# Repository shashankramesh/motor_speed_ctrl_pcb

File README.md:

# motor_speed_ctrl_pcb

The repository contains the schematic, PCB layout, arduino code and simulation of the motor speed controller.

The speed controller uses ATmega328P-PU SMD microcontroller and includes I2C/SPI/USART communication.
The PCB is also designed to be interfaced with incremental, absolute or potentiometer speed sensors. 
Two or more speed controllers can be daisy chained with I2C communication.

The arduino code uses the PID algorithm for controlling the speed of the motors.

The simulation uses continous and discrete models of the motor whose speed had to be controlled, for tuning the parameters of PID. 
This motor model can be replaced with the model of the motor that has to be controlled.

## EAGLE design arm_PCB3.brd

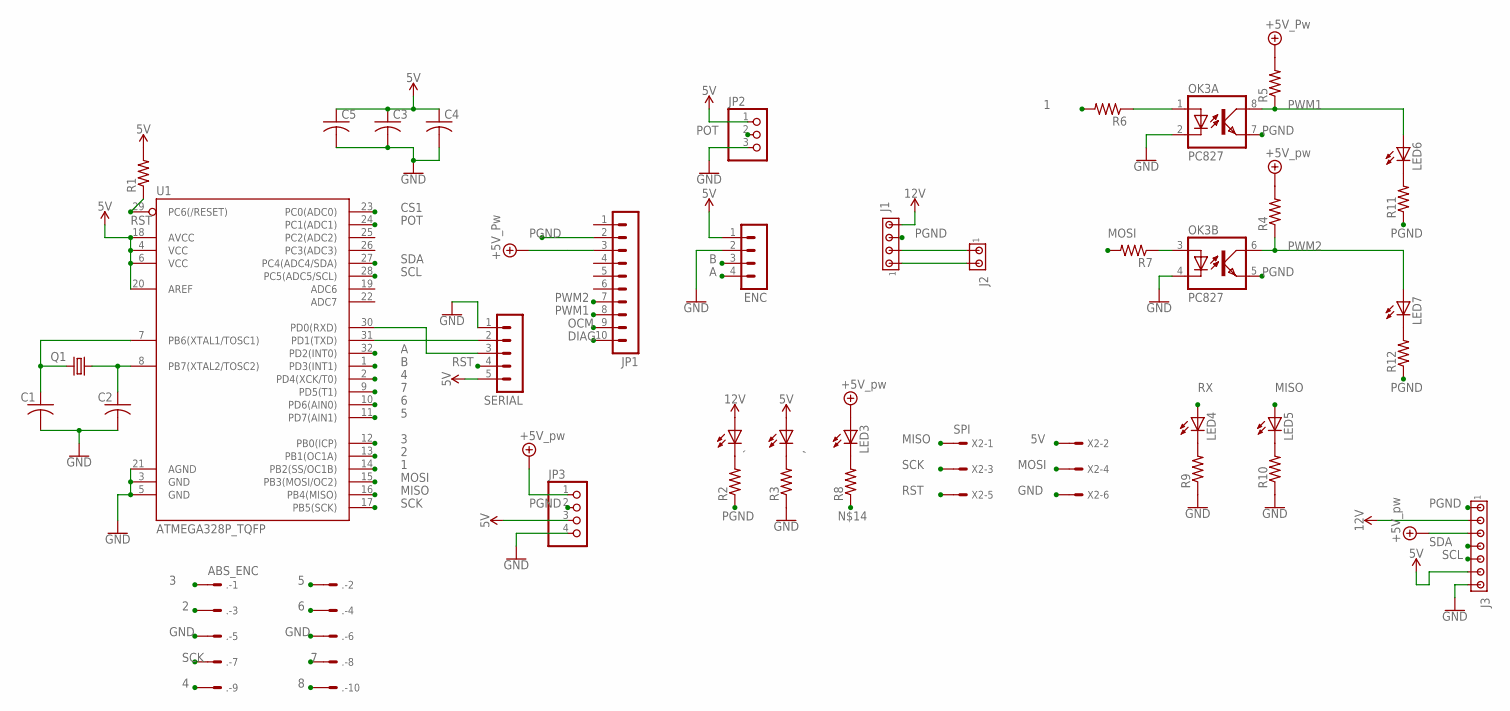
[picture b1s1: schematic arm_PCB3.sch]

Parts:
,: LEDSMT1206; 1206
.: ABS_ENC; 057-010-1
C1, C2: C-US025-024X044; C025-024X044
C3, C4, C5: C-USC1206; C1206
ENC: MA04-1
J1: MTA04-100; 10X04MTA
J2: MTA02-156; 1X2MTA
J3: MTA07-156; 1X7MTA
JP1: MA10-1
JP2: PINHD-1X3; 1X03
JP3: PINHD-1X4; 1X04
LED3, LED4, LED5, LED6, LED7: LEDSMT1206; 1206
OK3: PC827; DIL08
Q1: CRYSTALHC49U-V; HC49U-V
R1, R2, R3, R4, R5, R6, R7, R8, R9, R10, R11, R12: R-US_R0805; R0805
SERIAL: MA05-1
U1: ATMEGA328P_TQFP; TQFP32-08
X2: SPI; 057-006-1
`: LEDSMT1206; 1206

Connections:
1: R6.2, U1.14 (PB2(SS/OC1B))
2: ..3, U1.13 (PB1(OC1A))
3: ..1, U1.12 (PB0(ICP))
4: ..9, U1.2 (PD4(XCK/T0))
5: ..2, U1.11 (PD7(AIN1))
5V: ,.A, C3.1, C4.1, C5.1, ENC.1, J3.6, JP2.1, JP3.3, R1.2, SERIAL.5, U1.4 (VCC), U1.6 (VCC), U1.18 (AVCC), U1.20 (AREF), X2.2
6: ..4, U1.10 (PD6(AIN0))
7: ..8, U1.9 (PD5(T1))
8: ..10
12V: J1.4, J3.2, `.A
+5V: J3.3, JP1.3, JP3.1, LED3.A, R4.2, R5.2
A: ENC.4, U1.32 (PD2(INT0))
B: ENC.3, U1.1 (PD3(INT1))
CS1: U1.23 (PC0(ADC0))
DIAG: JP1.10
GND: ..5, ..6, C1.2, C2.2, C3.2, C4.2, C5.2, ENC.2, J3.7, JP2.3, JP3.4, OK3.2 (C), OK3.4 (C), R3.1, R9.1, R10.1, SERIAL.1, U1.3 (GND), U1.5 (GND), U1.21 (AGND), X2.6
MISO: LED5.A, U1.16 (PB4(MISO)), X2.1
MOSI: R7.2, U1.15 (PB3(MOSI/OC2)), X2.4
unnamed: C1.1, Q1.2, U1.7 (PB6(XTAL1/TOSC1))
unnamed: J1.2, J2.1
unnamed: C2.1, Q1.1, U1.8 (PB7(XTAL2/TOSC2))
unnamed: R2.2, `.C
unnamed: ,.C, R3.2
unnamed: J1.1, J2.2
unnamed: LED6.C, R11.2
unnamed: LED3.C, R8.2
unnamed: OK3.1 (A), R6.1
unnamed: OK3.3 (A), R7.1
unnamed: LED4.C, R9.2
unnamed: LED5.C, R10.2
unnamed: LED7.C, R12.2
OCM: JP1.9
PGND: J1.3, J3.1, JP1.2, JP3.2, OK3.5 (EMIT), OK3.7 (EMIT), R2.1, R11.1, R12.1
POT: JP2.2, U1.24 (PC1(ADC1))
PWM1: JP1.8, LED6.A, OK3.8 (COL), R5.1
PWM2: JP1.7, LED7.A, OK3.6 (COL), R4.1
RST: R1.1, SERIAL.4, U1.29 (PC6(/RESET)), X2.5
RX: LED4.A, SERIAL.3, U1.30 (PD0(RXD))
SCK: ..7, U1.17 (PB5(SCK)), X2.3
SCL: J3.5, U1.28 (PC5(ADC5/SCL))
SDA: J3.4, U1.27 (PC4(ADC4/SDA))
TX: SERIAL.2, U1.31 (PD1(TXD))

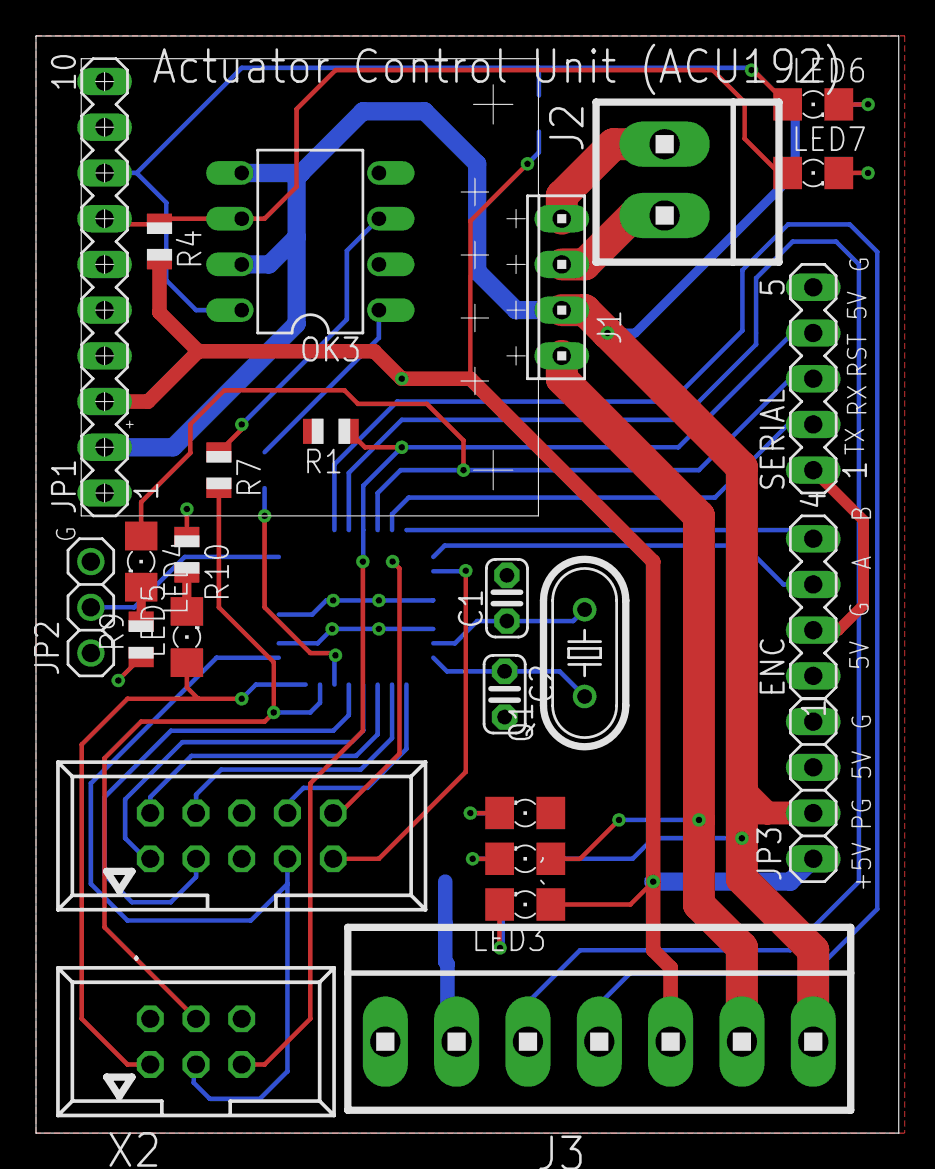
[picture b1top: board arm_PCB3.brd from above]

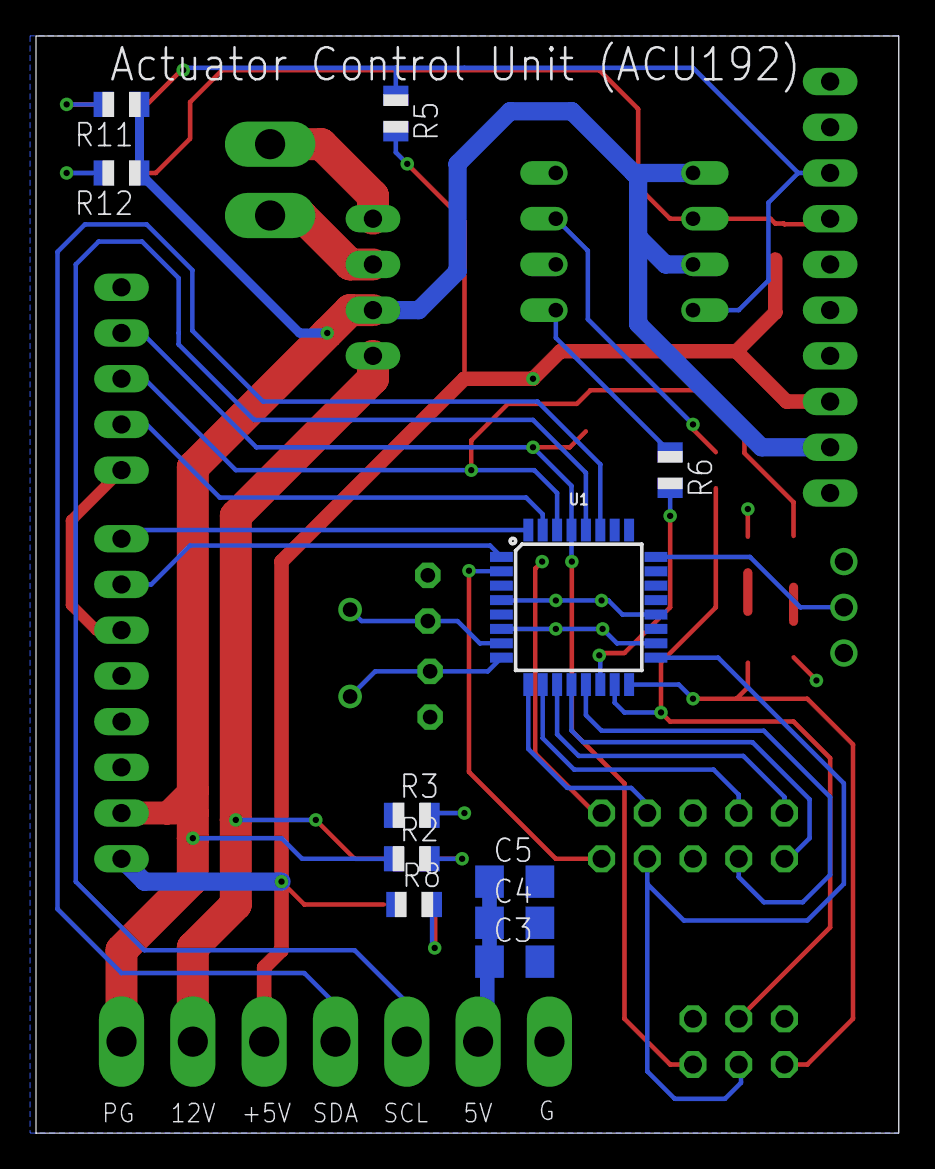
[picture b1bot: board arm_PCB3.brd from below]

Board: 2 copper layers, 47.9 x 61.0 mm, 37 parts (11 on the bottom side), 38 nets.

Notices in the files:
parts and their libraries:
SparkFun-IC-Microcontroller: Licensing: Creative Commons ShareAlike 4.0 International - https://creativecommons.org/licenses/by-sa/4.0
